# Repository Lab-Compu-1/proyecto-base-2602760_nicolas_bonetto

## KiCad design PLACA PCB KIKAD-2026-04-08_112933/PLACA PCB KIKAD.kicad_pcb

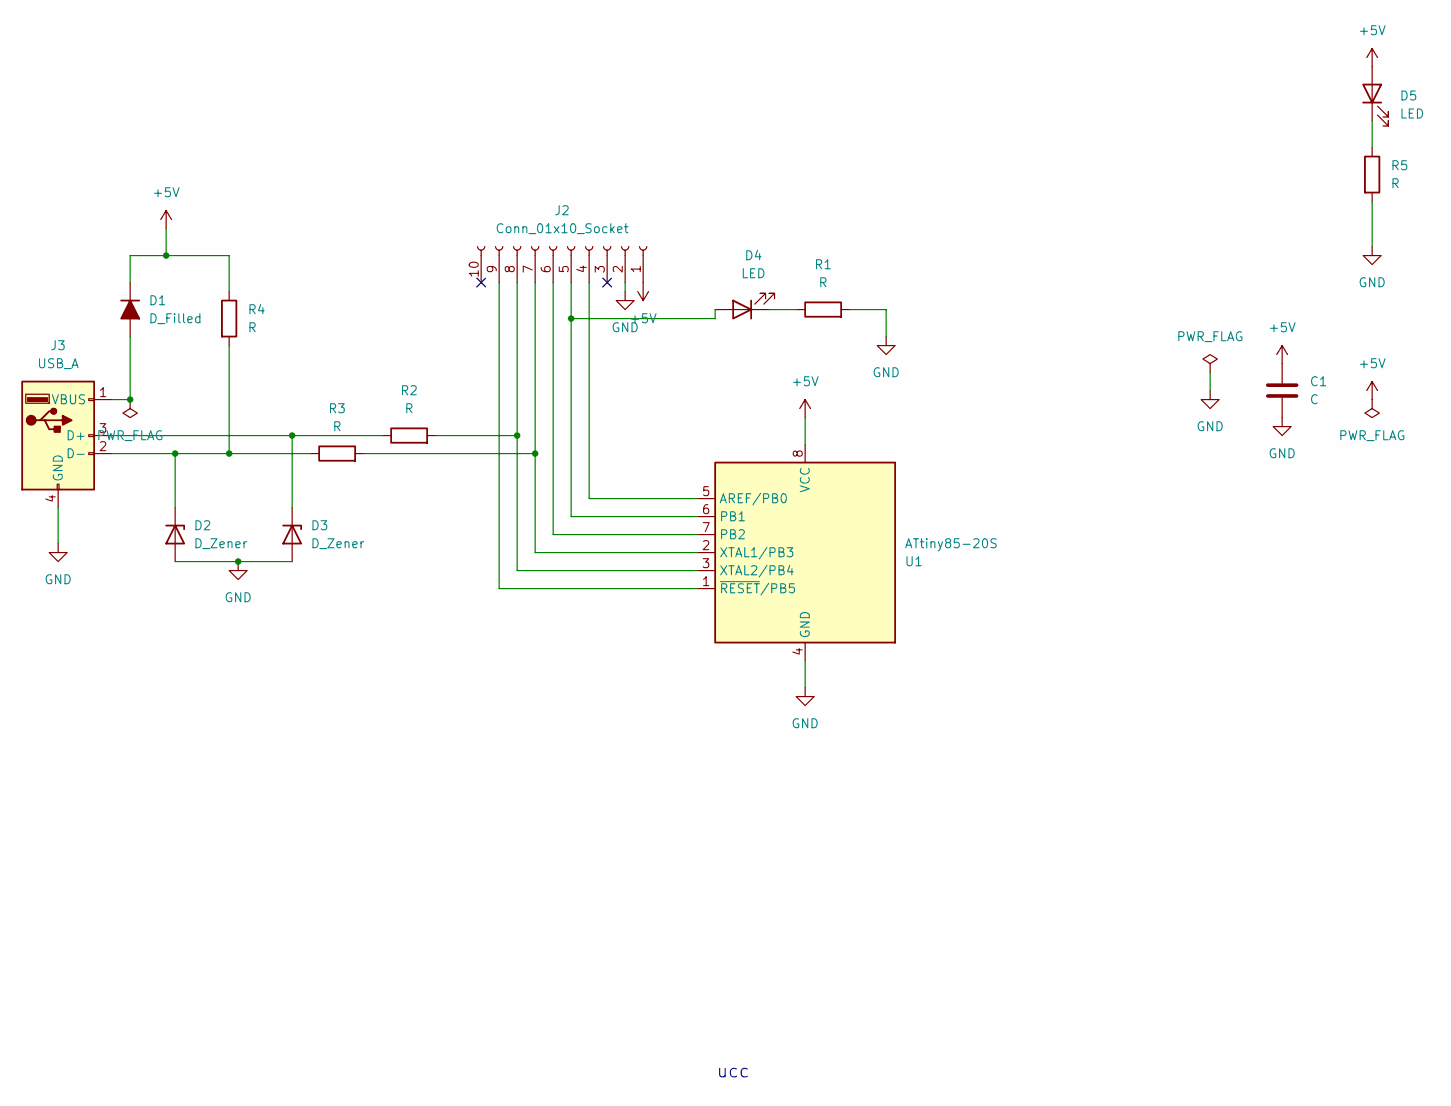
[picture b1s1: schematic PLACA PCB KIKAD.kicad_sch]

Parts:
C1: C; C_0805_2012Metric_Pad1.18x1.45mm_HandSolder
D1: D_Filled; D_MiniMELF_Handsoldering
D2, D3: D_Zener; D_SOD-123
D4, D5: LED; LED_0805_2012Metric
J2: Conn_01x10_Socket; PinSocket_1x10_P2.54mm_Vertical
J3: USB_A; USB_A_UCC
R1, R2, R3, R4, R5: R; R_0805_2012Metric_Pad1.20x1.40mm_HandSolder
U1: ATtiny85-20S; SOIC-8_5.3x5.3mm_P1.27mm

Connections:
+5V: C1.1, D1.1 (K), D5.2 (A), J2.1, R4.1, U1.8 (VCC)
GND: C1.2, D2.2 (A), D3.2 (A), J2.2, J3.4 (GND), R1.2, R5.2, U1.4 (GND)
unnamed: D1.2 (A), J3.1 (VBUS)
unnamed: D2.1 (K), J3.2 (D-), R3.1, R4.2
unnamed: D3.1 (K), J3.3 (D+), R2.1
unnamed: D4.2 (A), J2.5, U1.6 (PB1)
unnamed: D4.1 (K), R1.1
unnamed: D5.1 (K), R5.1
unnamed: J2.4, U1.5 (AREF/PB0)
unnamed: J2.6, U1.7 (PB2)
unnamed: J2.7, R3.2, U1.2 (XTAL1/PB3)
unnamed: J2.8, R2.2, U1.3 (XTAL2/PB4)
unnamed: J2.9, U1.1 (~RESET/PB5)

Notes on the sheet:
ucc

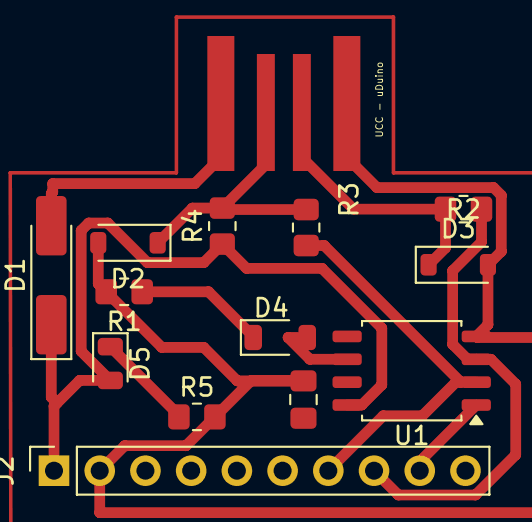
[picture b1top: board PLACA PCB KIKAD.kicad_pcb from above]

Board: 2 copper layers, 14 parts (0 on the bottom side), 13 nets.

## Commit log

2026-05-22 GitHub Classroom Feedback
2026-05-22 Setting up GitHub Classroom Feedback
2026-05-29 Mi primer commit y entrega de proyecto kikad
